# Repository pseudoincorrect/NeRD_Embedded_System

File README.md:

# Neural activity transmission device 

This repository describe the code of a neural activity transmission device embedded on a rodent.
The purpose of this system is to log the the electrical activity of a rat's neurones onto a computer.

## Global view of the acquisition system 

![alt text][global_system]

[global_system]: https://github.com/pseudoincorrect/Electrophy_Embedded_System/blob/doxygen/pictures/global_system.png?raw=true "Global data acquisition system"

### This repository contain the code and the eagle file necessary to create a the transmitting system embedded on the rodent (see above)

### Features (Embedded Part)

* Omnetics adapter
* Transmit 4 channels of 16 bits at 20 kHz 
* Or 8 channels compressed (16 bits after decompression) at 20 kHz
* Consume 18 mA at 3.7 V at full transmission load
* Weight 7 grams 
* Volume : 2cm *2cm * 2cm 

### Features (Interface Part)

* USB audio protocol interface to display and log on PC
* 8 channels DAC to connect to an acquisition card
* USB as power supply

## Technical part

On this version, we use the Microcontroler [STM32f051C8T7](http://www.st.com/web/en/catalog/mmc/SC1169/SS1574/LN7/PF251889) to interface the Intantech [RHD2132](http://www.intantech.com/products_RHD2000.html) ADC device, and the Nordic Semiconductor [Nrf24l01+](http://www.nordicsemi.com/eng/Products/2.4GHz-RF/nRF24L01) RF transciever.

Eagle files and manual provided in this repertory

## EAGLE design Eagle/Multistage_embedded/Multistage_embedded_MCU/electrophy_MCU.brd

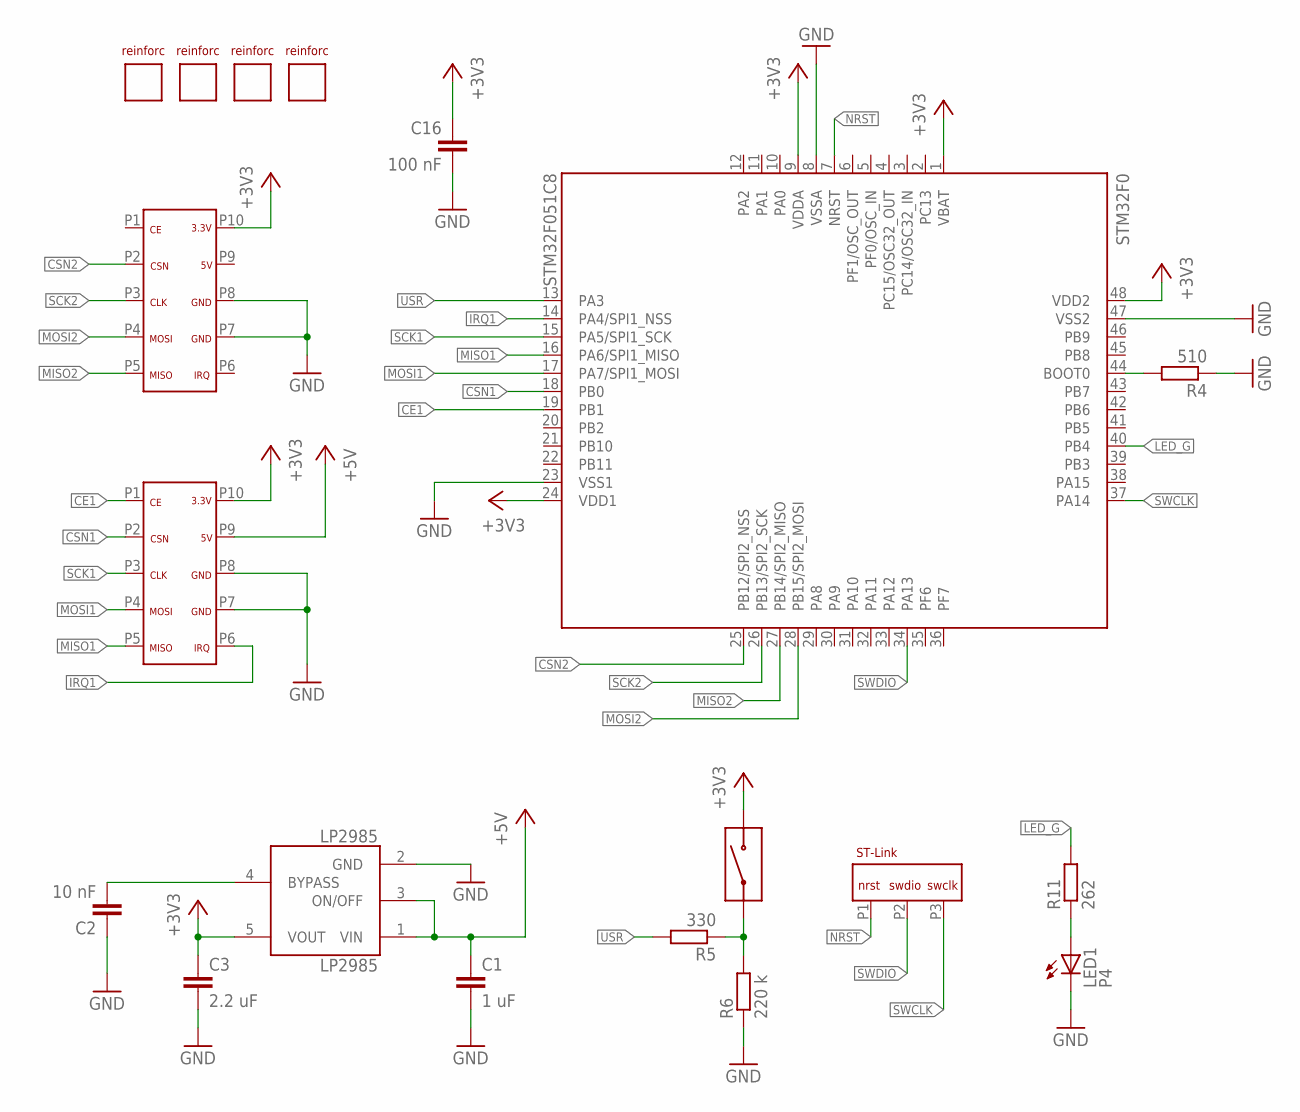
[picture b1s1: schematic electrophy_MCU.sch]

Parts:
C1: 1 uF; C0603
C2: 10 nF; C0603
C3: 2.2 uF; C0603
C16: 100 nF; C0603
LED1: P4; CHIPLED_0603
LP2985: LP2985AIM5-3.3; SOT25
R4: 510; R0603
R5: 330; R0603
R6: 220 k; R0603
R11: 262; R0603
STM32F0: STM32F051C8; LQFP48-7X7
U$1: DF12-10-FEMALE
U$2: PROGRAM_PIN
U$3: DF12-10-MALE
U$4: TACTILE_BUTTON_THROUGH
U$5, U$6, U$7, U$8: REINFORCEMENT

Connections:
+3V3: C3.1, C16.1, LP2985.5 (VOUT), STM32F0.1 (VBAT), STM32F0.9 (VDDA), STM32F0.24 (VDD1), STM32F0.48 (VDD2), U$1.P10, U$3.P10, U$4.P2 (2)
+5V: C1.1, LP2985.1 (VIN), LP2985.3 (ON/OFF), U$1.P9
BYPASS: C2.2, LP2985.4 (BYPASS)
CE1: STM32F0.19 (PB1), U$1.P1
CSN1: STM32F0.18 (PB0), U$1.P2
CSN2: STM32F0.25 (PB12/SPI2_NSS), U$3.P2
GND: C1.2, C2.1, C3.2, C16.2, LED1.C, LP2985.2 (GND), R4.1, R6.1, STM32F0.8 (VSSA), STM32F0.23 (VSS1), STM32F0.47 (VSS2), U$1.P7, U$1.P8, U$3.P7, U$3.P8
IRQ1: STM32F0.14 (PA4/SPI1_NSS), U$1.P6
LED_G: R11.2, STM32F0.40 (PB4)
MISO1: STM32F0.16 (PA6/SPI1_MISO), U$1.P5
MISO2: STM32F0.27 (PB14/SPI2_MISO), U$3.P5
MOSI1: STM32F0.17 (PA7/SPI1_MOSI), U$1.P4
MOSI2: STM32F0.28 (PB15/SPI2_MOSI), U$3.P4
unnamed: R5.1, R6.2, U$4.P1 (1)
unnamed: R4.2, STM32F0.44 (BOOT0)
unnamed: LED1.A, R11.1
NRST: STM32F0.7 (NRST), U$2.P1
SCK1: STM32F0.15 (PA5/SPI1_SCK), U$1.P3
SCK2: STM32F0.26 (PB13/SPI2_SCK), U$3.P3
SWCLK: STM32F0.37 (PA14), U$2.P3
SWDIO: STM32F0.34 (PA13), U$2.P2
USR: R5.2, STM32F0.13 (PA3)

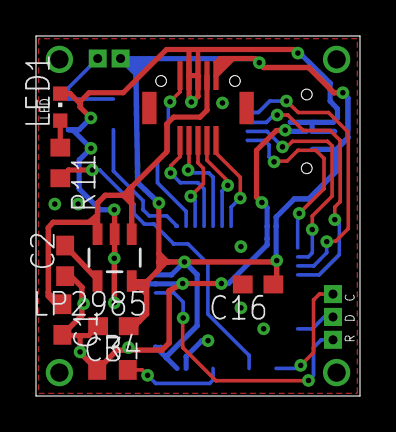
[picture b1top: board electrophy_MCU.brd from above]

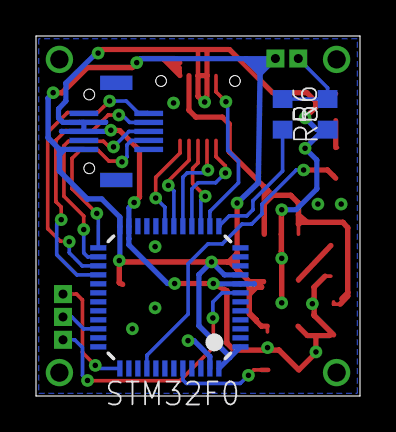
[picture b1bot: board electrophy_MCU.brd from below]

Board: 2 copper layers, 18.0 x 20.0 mm, 19 parts (5 on the bottom side), 22 nets.

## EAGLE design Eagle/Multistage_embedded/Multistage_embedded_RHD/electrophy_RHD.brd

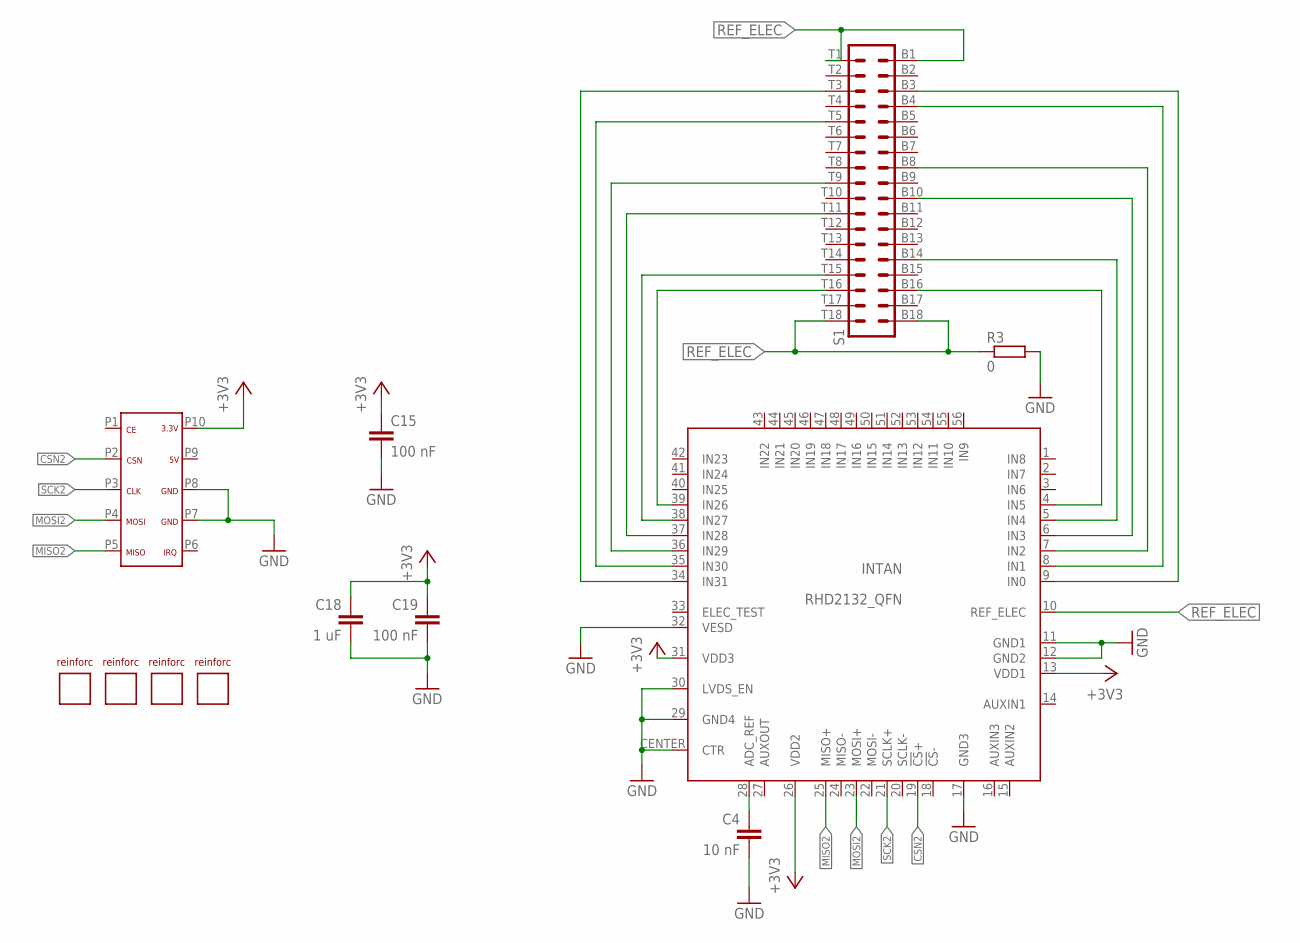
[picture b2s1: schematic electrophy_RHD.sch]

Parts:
C4: 10 nF; C0603
C15, C19: 100 nF; C0603
C18: 1 uF; C0603
INTAN: RHD2132_QFN; QFN56_8_X_8_LARGE
R3: 0; R0603
S1: OMNETICS_A79027
U$1: DF12-10-FEMALE
U$2, U$3, U$4, U$5: REINFORCEMENT

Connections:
+3V3: C15.1, C18.1, C19.1, INTAN.13 (VDD1), INTAN.26 (VDD2), INTAN.31 (VDD3), U$1.P10
CSN2: INTAN.19 (!CS!+), U$1.P2
GND: C4.2, C15.2, C18.2, C19.2, INTAN.11 (GND1), INTAN.12 (GND2), INTAN.17 (GND3), INTAN.29 (GND4), INTAN.30 (LVDS_EN), INTAN.32 (VESD), INTAN.CENTER (CTR), R3.2, U$1.P7, U$1.P8
MISO2: INTAN.25 (MISO+), U$1.P5
MOSI2: INTAN.23 (MOSI+), U$1.P4
unnamed: INTAN.4 (IN5), S1.B16
unnamed: INTAN.34 (IN31), S1.T3
unnamed: INTAN.35 (IN30), S1.T5
unnamed: INTAN.38 (IN27), S1.T15
unnamed: INTAN.39 (IN26), S1.T16
unnamed: C4.1, INTAN.28 (ADC_REF)
unnamed: INTAN.8 (IN1), S1.B4
unnamed: INTAN.9 (IN0), S1.B3
unnamed: INTAN.5 (IN4), S1.B14
unnamed: INTAN.7 (IN2), S1.B8
unnamed: INTAN.6 (IN3), S1.B10
unnamed: INTAN.36 (IN29), S1.T9
unnamed: INTAN.37 (IN28), S1.T11
REF_ELEC: INTAN.10 (REF_ELEC), R3.1, S1.B1, S1.B18, S1.T1, S1.T18
SCK2: INTAN.21 (SCLK+), U$1.P3

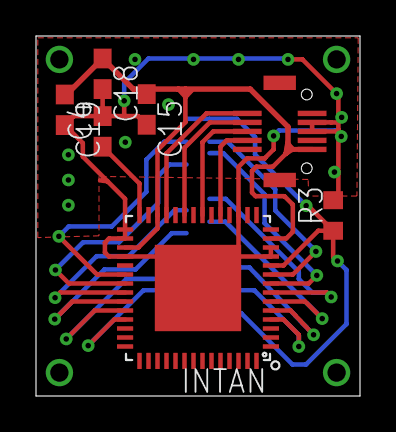
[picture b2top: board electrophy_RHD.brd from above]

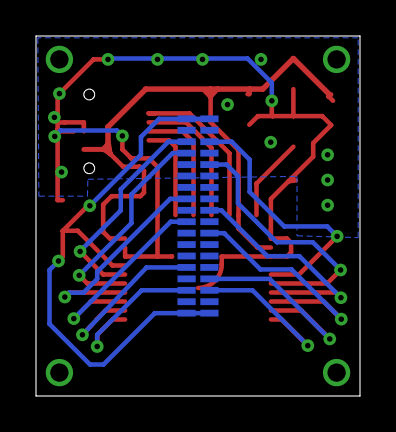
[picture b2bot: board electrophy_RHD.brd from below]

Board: 2 copper layers, 18.0 x 20.0 mm, 12 parts (2 on the bottom side), 20 nets.

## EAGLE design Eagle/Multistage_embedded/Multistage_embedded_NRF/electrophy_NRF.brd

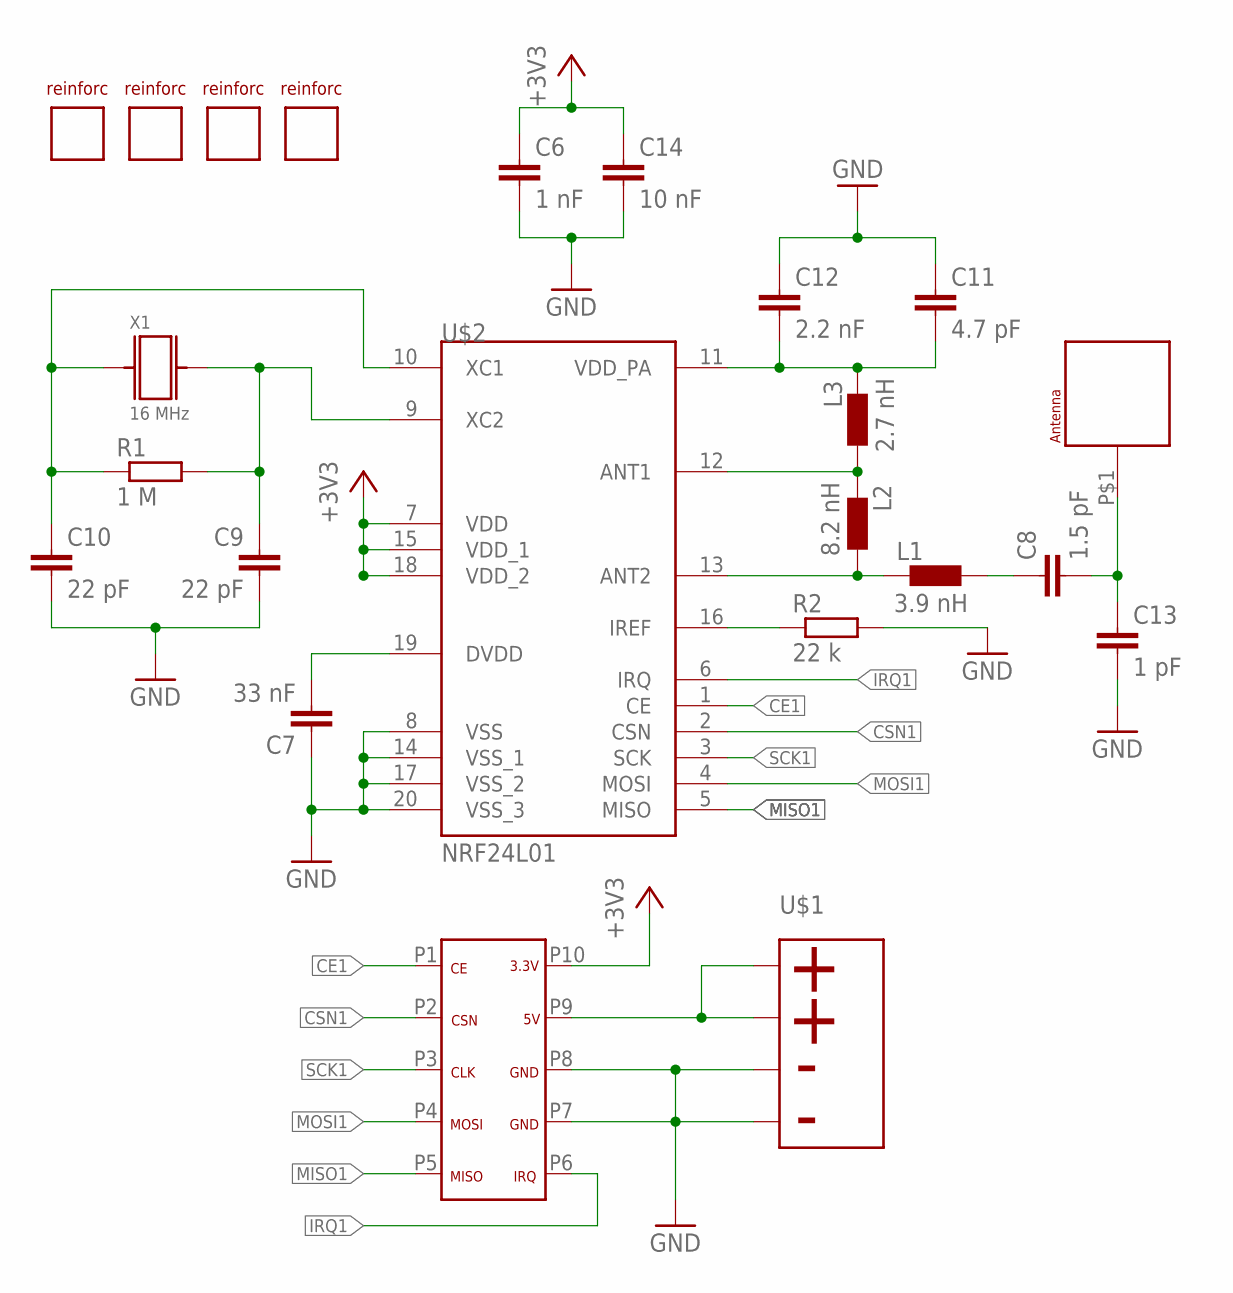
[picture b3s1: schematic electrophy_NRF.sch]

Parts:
C6: 1 nF; C0603
C7: 33 nF; C0603
C8: 1.5 pF; C0603
C9, C10: 22 pF; C0603
C11: 4.7 pF; C0603
C12: 2.2 nF; C0603
C13: 1 pF; C0603
C14: 10 nF; C0603
L1: 3.9 nH; C0603
L2: 8.2 nH; C0603
L3: 2.7 nH; C0603
R1: 1 M; R0603
R2: 22 k; R0603
U$1: BAT_HOLDER
U$2: NRF24L01; QFN20
U$3: WURTH_ANTENNA
U$4: DF12-10-MALE
U$5, U$6, U$7, U$8: REINFORCEMENT
X1: 16 MHz; NRF_XTAL

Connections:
+3V3: C6.1, C14.1, U$2.7 (VDD), U$2.15 (VDD_1), U$2.18 (VDD_2), U$4.P10
CE1: U$2.1 (CE), U$4.P1
CSN1: U$2.2 (CSN), U$4.P2
GND: C6.2, C7.1, C9.2, C10.2, C11.1, C12.1, C13.2, C14.2, R2.2, U$1.PMOINS, U$1.PMOINSBIS, U$2.8 (VSS), U$2.14 (VSS_1), U$2.17 (VSS_2), U$2.20 (VSS_3), U$4.P7, U$4.P8
IRQ1: U$2.6 (IRQ), U$4.P6
MISO1: U$2.5 (MISO), U$4.P5
MOSI1: U$2.4 (MOSI), U$4.P4
unnamed: C7.2, U$2.19 (DVDD)
unnamed: C11.2, C12.2, L3.2, U$2.11 (VDD_PA)
unnamed: R2.1, U$2.16 (IREF)
unnamed: L1.2, L2.1, U$2.13 (ANT2)
unnamed: C9.1, R1.2, U$2.9 (XC2), X1.P$1 (1)
unnamed: L2.2, L3.1, U$2.12 (ANT1)
unnamed: C8.2, C13.1, U$3.P$1
unnamed: C8.1, L1.1
unnamed: C10.1, R1.1, U$2.10 (XC1), X1.P$2 (2)
PPLUS: U$1.PPLUS, U$1.PPLUSBIS, U$4.P9
SCK1: U$2.3 (SCK), U$4.P3

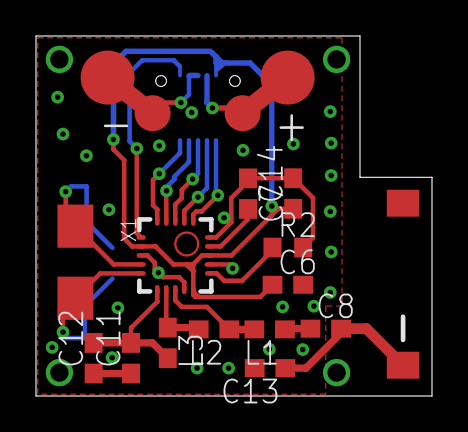
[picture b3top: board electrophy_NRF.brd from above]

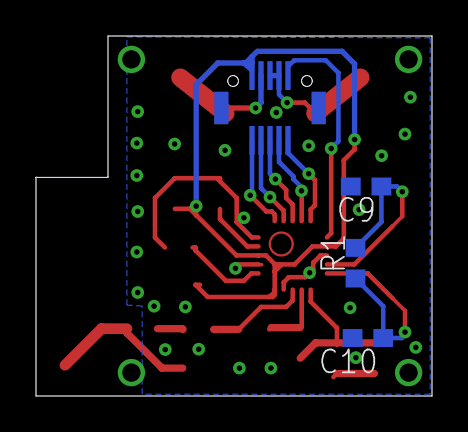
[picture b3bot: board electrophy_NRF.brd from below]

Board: 2 copper layers, 22.0 x 20.0 mm, 23 parts (4 on the bottom side), 18 nets.

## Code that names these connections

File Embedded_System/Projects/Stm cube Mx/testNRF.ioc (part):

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Mcu.Name=STM32F051C8Tx
Mcu.Package=LQFP48
Mcu.UserName=STM32F051C8Tx
PA15.Signal=GPIO_Input
PA4.GPIOParameters=GPIO_PuPd,GPIO_Label,GPIO_Mode
PA4.GPIO_Label=Spi1Nss
PA4.GPIO_Mode=GPIO_MODE_INPUT
PA4.GPIO_PuPd=GPIO_NOPULL
PA4.Signal=GPIO_Input
PA5.Mode=Full_Duplex_Master
PA5.Signal=SPI1_SCK
PA6.Mode=Full_Duplex_Master
PA6.Signal=SPI1_MISO
PA7.Mode=Full_Duplex_Master
PA7.Signal=SPI1_MOSI
PB0.Signal=GPIO_Output
PB1.Signal=GPIO_Output
PB13.Mode=Full_Duplex_Master
PB13.Signal=SPI2_SCK
PB14.Mode=Full_Duplex_Master
PB14.Signal=SPI2_MISO
PB15.Mode=Full_Duplex_Master
PB15.Signal=SPI2_MOSI
PB4.Signal=GPIO_Output
PB5.Signal=GPIO_Output
PF7.Signal=GPIO_Output
RCC.SYSCLKFreq_VALUE=48000000
RCC.SYSCLKSource=RCC_SYSCLKSOURCE_PLLCLK

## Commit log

2015-03-25 :octocat: Added .gitattributes & .gitignore files
2015-04-20 implementation of the FBAR compression
2015-04-20 add files compression
2015-04-21 compression workit analyser
2015-04-21 compression steady
2015-04-22 compress and reset implementation
2015-04-23 implement compression with balise
2015-05-05 compression test, bug in uncompression ?
2015-05-07 working compression, with warning array range in FBAR.c : adaptcutvalues
2015-05-13 compression 17 KHz
2015-05-27 Readme commit
2015-05-27 read me
2015-05-29 readme
2015-06-09 base comm ok
2015-06-09 usb + alls state OK
2015-06-12 Change state ok, both
2015-06-18 communication OK, plus RHD neaw system
2015-06-20 Leds Ok , fbar to improve, rhd chanel selction and DAC to test
2015-06-23 compression fixed, remain reinit Fbar to do
2015-06-23 Upload before Lyon
2015-06-30 before new branch (packet NRF size change)
2015-07-01 before workshop
2015-07-28 firt commit of testSystem. modification to quantifie the loss of the wireless transmission
2015-07-30 successful test
2015-08-03 commit before basement tests
2015-08-11 new compression 3 bits
2015-08-11 white commit
2015-08-11 before lab test
2015-08-12 no change
2015-09-08 doxygen first
2015-10-05 ADCPM
2015-10-06 ADCPM working
2015-10-14 reinitialization ADCPM working
2015-10-19 ADCPM eta and Beta setable OK
2015-10-21 ADCPM Updtate
2015-10-27 markedown update
2015-11-09 before merge master
2015-11-10 comparaison compression non compression sur 2 cannaux
2015-11-12 before Lyon
2015-11-12 adding project files
2015-12-18 common include changed
2017-07-05 add supportive file
    add supportive file
    manual
    eagle file
2017-07-05 Add description
